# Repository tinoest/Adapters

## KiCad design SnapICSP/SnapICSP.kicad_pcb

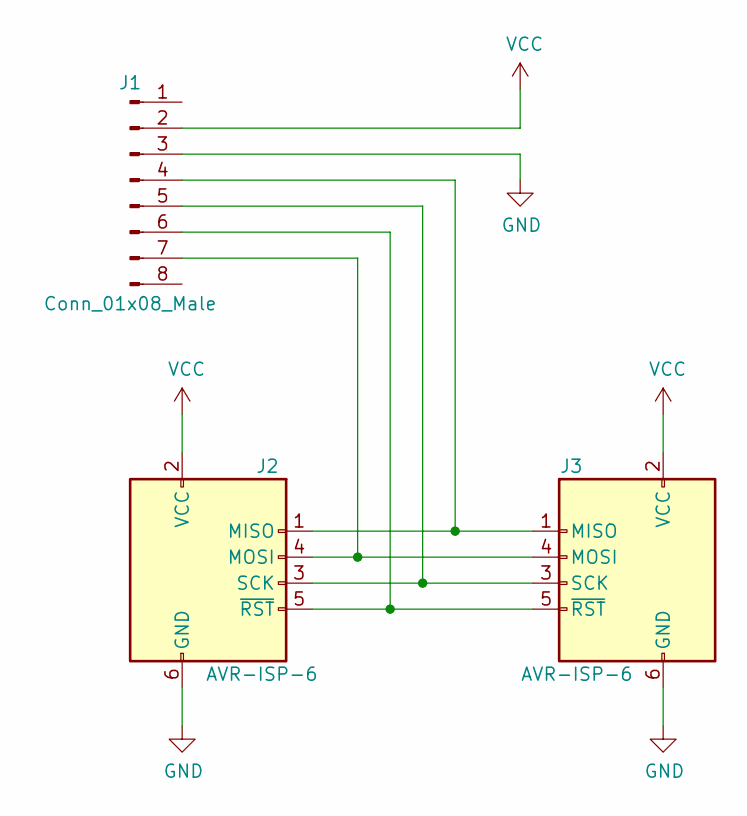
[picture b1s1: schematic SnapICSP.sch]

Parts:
J1: Conn_01x08_Male; Pin_Header_Angled_1x08_Pitch2.54mm
J2: AVR-ISP-6; Pin_Header_Straight_2x03_Pitch2.00mm
J3: AVR-ISP-6; Pin_Header_Straight_2x03_Pitch2.54mm

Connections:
GND: J1.3, J2.6 (GND), J3.6 (GND)
unnamed: J1.4, J2.1 (MISO), J3.1 (MISO)
unnamed: J1.5, J2.3 (SCK), J3.3 (SCK)
unnamed: J1.6, J2.5 (~RST), J3.5 (~RST)
unnamed: J1.7, J2.4 (MOSI), J3.4 (MOSI)
VCC: J1.2, J2.2 (VCC), J3.2 (VCC)

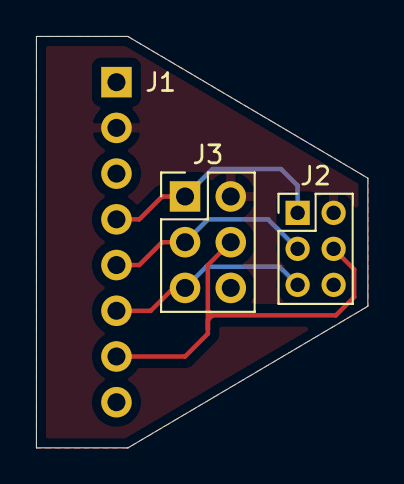
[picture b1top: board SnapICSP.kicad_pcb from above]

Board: 2 copper layers, 18.4 x 22.9 mm, 3 parts (1 on the bottom side), 6 nets.

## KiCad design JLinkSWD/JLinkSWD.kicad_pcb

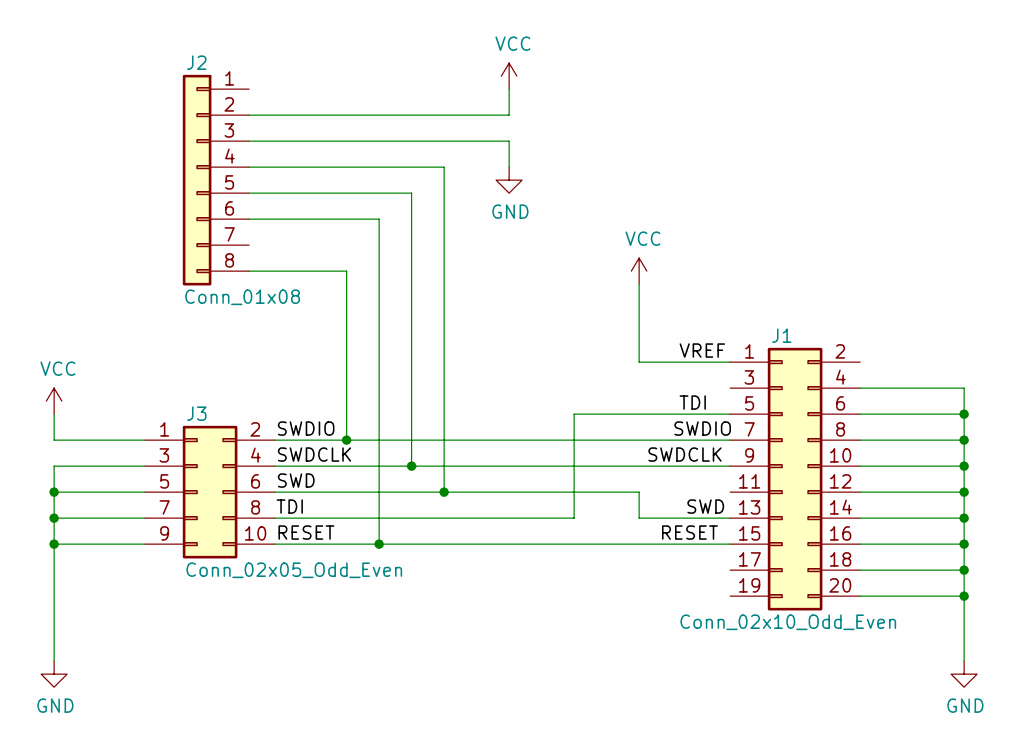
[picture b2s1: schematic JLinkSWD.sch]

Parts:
J1: Conn_02x10_Odd_Even; Socket_Strip_Straight_2x10_Pitch2.54mm
J2: Conn_01x08; Socket_Strip_Straight_1x08_Pitch2.54mm
J3: Conn_02x05_Odd_Even; Socket_Strip_Straight_2x05_Pitch1.27mm

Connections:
/RESET: J1.15, J2.6, J3.10
/SWD: J1.13, J2.4, J3.6
/SWDCLK: J1.9, J2.5, J3.4
/SWDIO: J1.7, J2.8, J3.2
/TDI: J1.5, J3.8
GND: J1.4, J1.6, J1.8, J1.10, J1.12, J1.14, J1.16, J1.18, J1.20, J2.3, J3.3, J3.5, J3.7, J3.9
VCC: J1.1, J2.2, J3.1

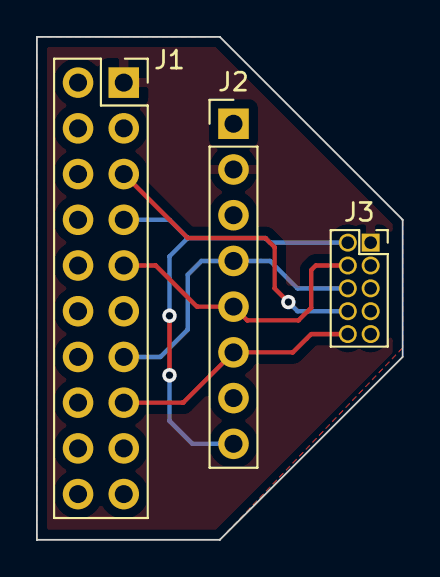
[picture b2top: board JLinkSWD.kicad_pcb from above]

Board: 2 copper layers, 20.3 x 27.9 mm, 3 parts (0 on the bottom side), 7 nets.

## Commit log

2020-06-06 Reduced PCB size
2020-06-11 Corrected pinout on component
